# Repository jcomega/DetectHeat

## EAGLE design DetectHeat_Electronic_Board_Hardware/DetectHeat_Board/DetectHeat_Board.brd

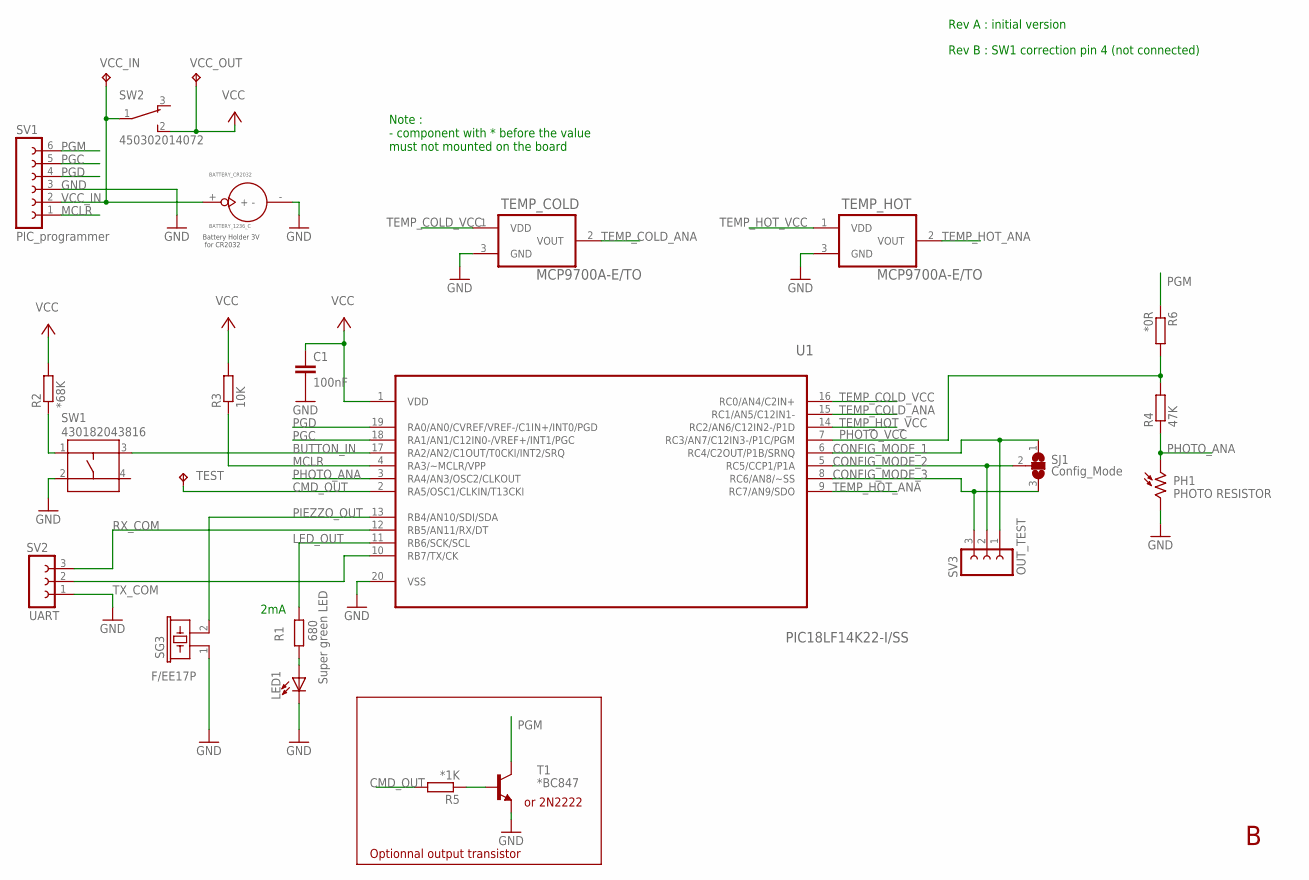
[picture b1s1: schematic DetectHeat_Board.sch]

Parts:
BATTERY_CR2032: BATTERY_1236_C
C1: 100nF; C0805
LED1: Super green LED; CHIPLED_0805
PH1: PHOTO RESISTOR; T0-46-A10XX
R1: 680; R0805
R2: *68K; R0805
R3: 10K; R0805
R4: 47K; R0805
R5: *1K; R0805
R6: *0R; R0805
SG3: F/EE17P
SJ1: Config_Mode; SJ_2
SV1: PIC_programmer; FE06
SV2: UART; FE03-1
SV3: OUT_TEST; FE03-1
SW1: 430182043816
SW2: 450302014072
T1: *BC847; SOT23
TEMP_COLD: MCP9700A-E/TO; TO127P254X533-3
TEMP_HOT: MCP9700A-E/TO; TO127P254X533-3
TEST: TPPAD1-13; P1-13
U1: PIC18LF14K22-I/SS; SOP65P780X200-20N
VCC_IN: TPPAD1-13; P1-13
VCC_OUT: TPPAD1-13; P1-13

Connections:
BUTTON_IN: SW1.3, U1.17 (RA2/AN2/C1OUT/T0CKI/INT2/SRQ)
CMD_OUT: R5.2, TEST.TP, U1.2 (RA5/OSC1/CLKIN/T13CKI)
CONFIG_MODE_1: SJ1.1, SV3.1, U1.6 (RC4/C2OUT/P1B/SRNQ)
CONFIG_MODE_2: SJ1.2, SV3.2, U1.5 (RC5/CCP1/P1A)
CONFIG_MODE_3: SJ1.3, SV3.3, U1.8 (RC6/AN8/~SS)
GND: BATTERY_CR2032.-, C1.2, LED1.C, PH1.2, SG3.1, SV1.3, SV2.1, SW1.2, T1.2 (E), TEMP_COLD.3 (GND), TEMP_HOT.3 (GND), U1.20 (VSS)
LED_OUT: R1.1, U1.11 (RB6/SCK/SCL)
MCLR: R3.1, SV1.1, U1.4 (RA3/~MCLR/VPP)
unnamed: LED1.A, R1.2
unnamed: R5.1, T1.1 (B)
unnamed: R2.1, SW1.1
PGC: SV1.5, U1.18 (RA1/AN1/C12IN0-/VREF+/INT1/PGC)
PGD: SV1.4, U1.19 (RA0/AN0/CVREF/VREF-/C1IN+/INT0/PGD)
PGM: R6.1, SV1.6, T1.3 (C)
PHOTO_ANA: PH1.1, R4.1, U1.3 (RA4/AN3/OSC2/CLKOUT)
PHOTO_VCC: R4.2, R6.2, U1.7 (RC3/AN7/C12IN3-/P1C/PGM)
PIEZZO_OUT: SG3.2, U1.13 (RB4/AN10/SDI/SDA)
RX_COM: SV2.3, U1.12 (RB5/AN11/RX/DT)
TEMP_COLD_ANA: TEMP_COLD.2 (VOUT), U1.15 (RC1/AN5/C12IN1-)
TEMP_COLD_VCC: TEMP_COLD.1 (VDD), U1.16 (RC0/AN4/C2IN+)
TEMP_HOT_ANA: TEMP_HOT.2 (VOUT), U1.9 (RC7/AN9/SDO)
TEMP_HOT_VCC: TEMP_HOT.1 (VDD), U1.14 (RC2/AN6/C12IN2-/P1D)
TX_COM: SV2.2, U1.10 (RB7/TX/CK)
VCC: C1.1, R2.2, R3.2, SW2.2, U1.1 (VDD), VCC_OUT.TP
VCC_IN: BATTERY_CR2032.+, SV1.2, SW2.1, VCC_IN.TP

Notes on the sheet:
Note : - component with * before the value must not mounted on the board
2mA
Battery Holder 3V for CR2032
Optionnal output transistor
or 2N2222
Rev A : initial version
Rev B : SW1 correction pin 4 (not connected)

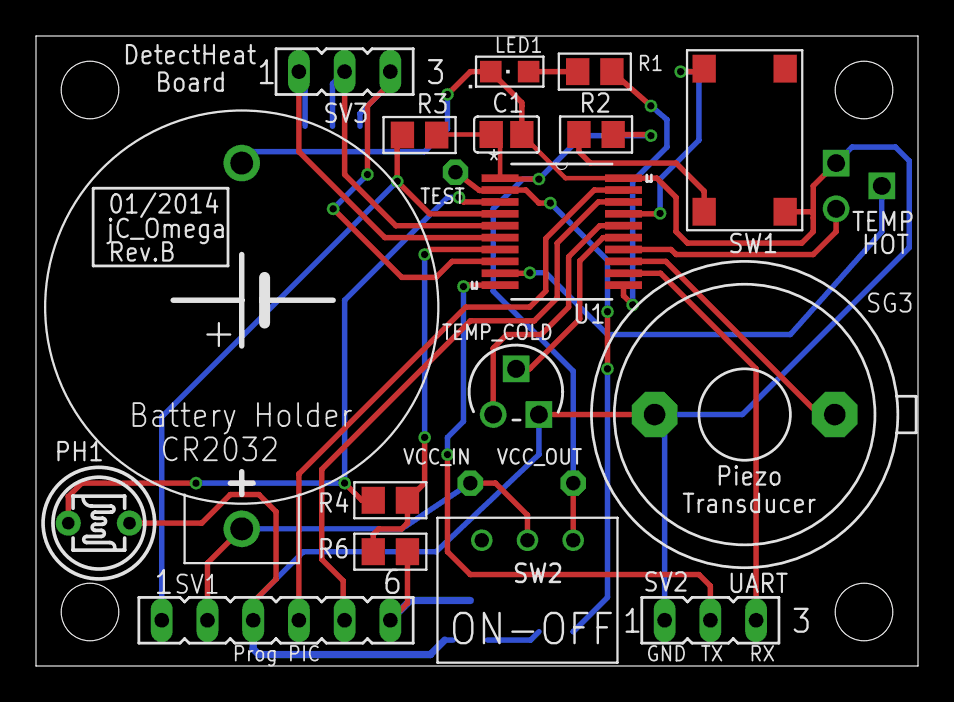
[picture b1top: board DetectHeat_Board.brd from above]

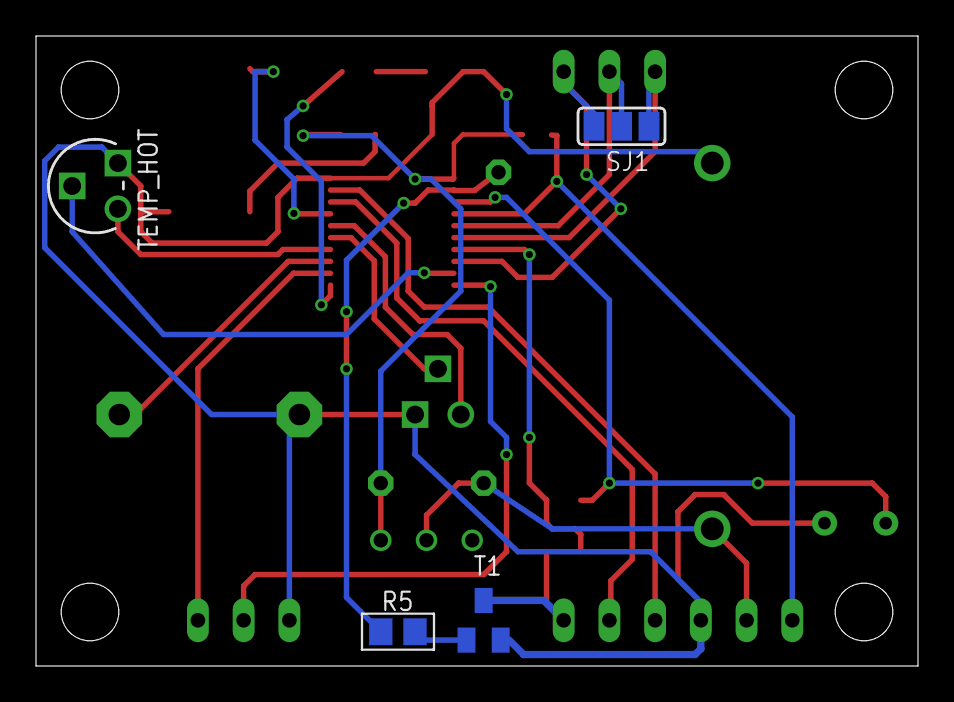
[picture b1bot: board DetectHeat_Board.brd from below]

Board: 4 copper layers, 49.0 x 35.0 mm, 24 parts (4 on the bottom side), 25 nets.

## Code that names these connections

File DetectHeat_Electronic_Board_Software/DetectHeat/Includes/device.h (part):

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
//@{

    #define READ_DIGITAL_INPUT0 PORTAbits.RA2
    #define READ_DIGITAL_INPUT1 PORTAbits.RA3

    #define TRIS_DIGITAL_OUTPUT0 TRISBbits.TRISB6
    #define READ_DIGITAL_OUTPUT0 PORTBbits.RB6
    #define SET_DIGITAL_OUTPUT0 LATBbits.LATB6

//@{
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//  INPUT/OUTPUT FOR PGD/PGC
    #define TRIS_PGD       TRISAbits.TRISA0
    #define SET_PGD        LATAbits.LATA0
    #define READ_PGD       PORTAbits.RA0

    #define TRIS_PGC       TRISAbits.TRISA1
    #define SET_PGC        LATAbits.LATA1
    #define READ_PGC       PORTAbits.RA1

//  INPUT/OUTPUT FOR BUTTON INPUT
    #define TRIS_BUTTON_IN       TRISAbits.TRISA2
    #define SET_BUTTON_IN        LATAbits.LATA2
    #define READ_BUTTON_IN       PORTAbits.RA2

//  INPUT/OUTPUT FOR COMMAND OUTPUT
    #define TRIS_CMD_OUT       TRISAbits.TRISA5
    #define SET_CMD_OUT        LATAbits.LATA5
    #define READ_CMD_OUT       PORTAbits.RA5

//  INPUT/OUTPUT FOR PIEZZO BUZZER
    #define TRIS_PIEZZO_OUT       TRISBbits.TRISB4
    #define SET_PIEZZO_OUT        LATBbits.LATB4
    #define READ_PIEZZO_OUT       PORTBbits.RB4

//  INPUT/OUTPUT FOR LED STATUS
    #define TRIS_LED_OUT       TRISBbits.TRISB6
    #define SET_LED_OUT        LATBbits.LATB6
    #define READ_LED_OUT       PORTBbits.RB6

// INPUT/OUTPUT FOR PHOTO RESISTOR
    #define TRIS_PHOTO_VCC        TRISCbits.TRISC3
    #define SET_PHOTO_VCC         LATCbits.LATC3
    #define READ_PHOTO_VCC        PORTCbits.RC3

    #define TRIS_PHOTO_ANALOG    TRISAbits.TRISA4
    #define ANA_PHOTO_ANALOG     3                  //AN3
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
    #define TRIS_TEMP_COLD_VCC       TRISCbits.TRISC0
    #define SET_TEMP_COLD_VCC        LATCbits.LATC0
    #define READ_TEMP_COLD_VCC       PORTCbits.RC0

    #define TRIS_TEMP_HOT_VCC        TRISCbits.TRISC2
    #define SET_TEMP_HOT_VCC         LATCbits.LATC2
    #define READ_TEMP_HOT_VCC        PORTCbits.RC2

//  INPUT/OUTPUT FOR CONFIG MODE
    #define TRIS_CONFIG_MODE_1       TRISCbits.TRISC4
    #define SET_CONFIG_MODE_1        LATCbits.LATC4
    #define READ_CONFIG_MODE_1       PORTCbits.RC4
    #define PWM_OUTPUT1              LATCbits.LATC4    // PWM output for red (test)

    #define TRIS_CONFIG_MODE_2       TRISCbits.TRISC5
    #define SET_CONFIG_MODE_2        LATCbits.LATC5
    #define READ_CONFIG_MODE_2       PORTCbits.RC5
    #define PWM_OUTPUT2              LATCbits.LATC5    // PWM output for green (test)

    #define TRIS_CONFIG_MODE_3       TRISCbits.TRISC6
    #define SET_CONFIG_MODE_3        LATCbits.LATC6
    #define READ_CONFIG_MODE_3       PORTCbits.RC6
    #define PWM_OUTPUT3              LATCbits.LATC6    // PWM output for blue (test)

    #define INPUT_PIN 1
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
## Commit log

2014-04-12 first version
2014-04-12 first commit v2
2014-04-12 add pictures
2014-04-12 minor update
2014-04-14 add Bill of material for the board
2014-04-14 correct little mistake : PIC reference
    PIC18F14K22 --> PIC18LF14K22 (low energy)

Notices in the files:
parts and their libraries:
Eagle_Wuerth_Elektronik_Switch_Power_Ele: Copyright: Würth Elektronik
